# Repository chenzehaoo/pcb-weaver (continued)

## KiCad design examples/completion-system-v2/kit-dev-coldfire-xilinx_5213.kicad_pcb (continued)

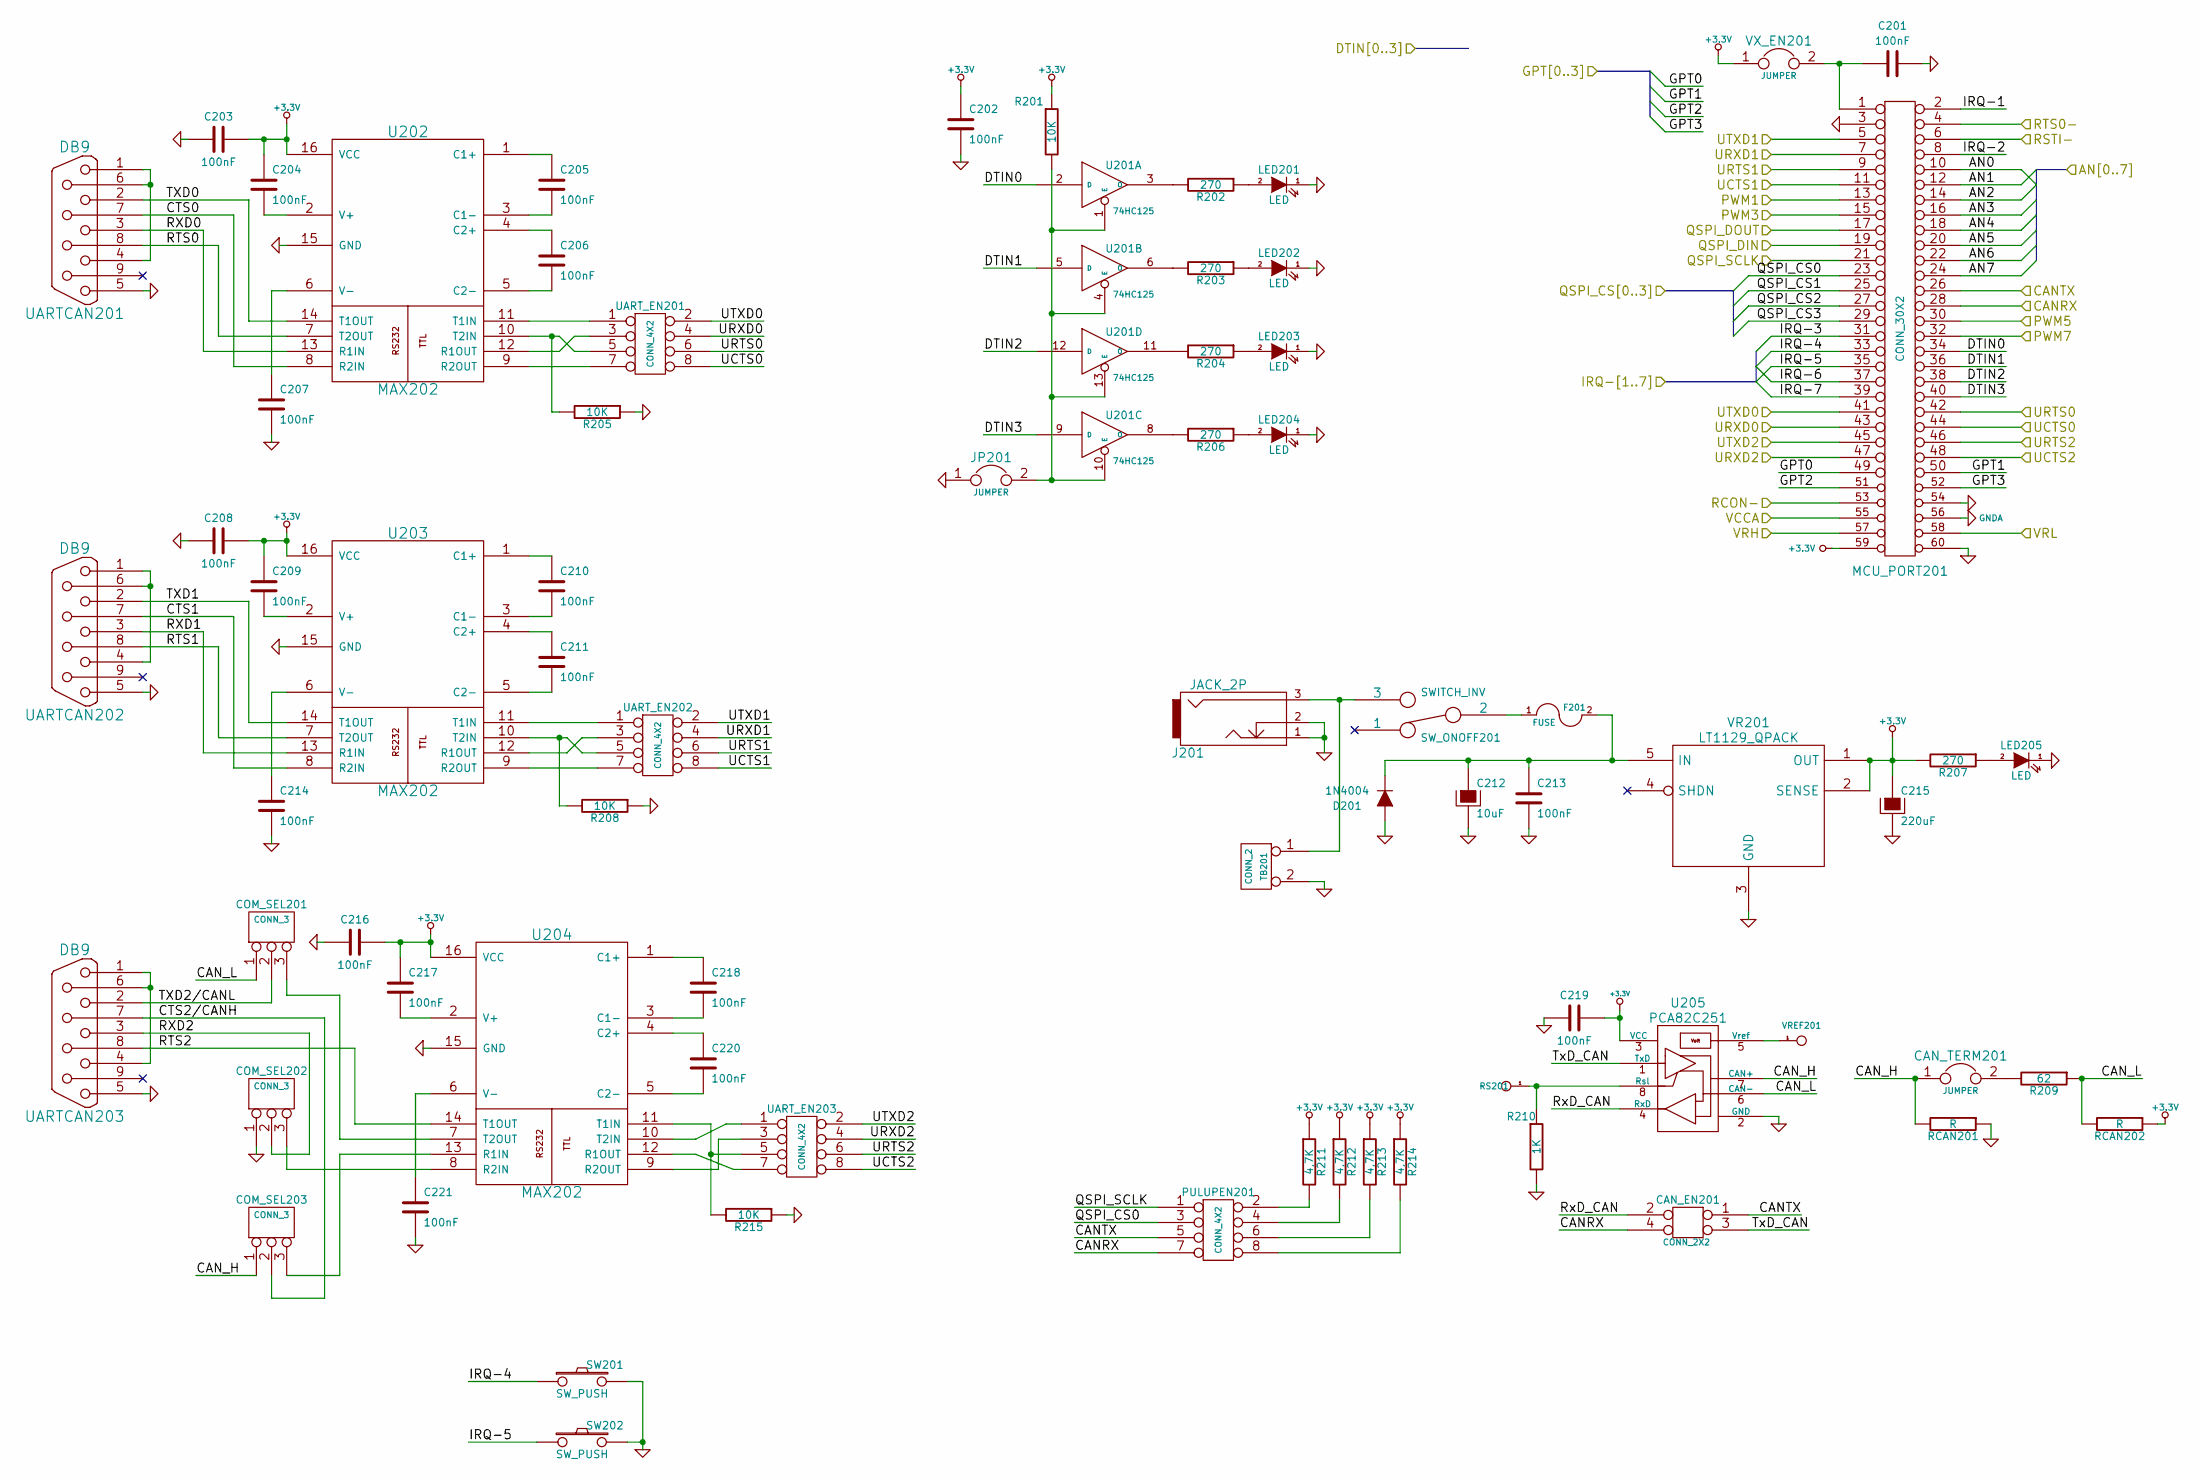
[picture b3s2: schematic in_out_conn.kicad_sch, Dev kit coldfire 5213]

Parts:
C201, C202, C203, C204, C205, C206, C207, C208, C209, C210, C211, C213, C214, C216, C217, C218, C219, C220, C221: 100nF; C_0805_2012Metric
C212: 10uF; CP_Radial_D8.0mm_P5.00mm
C215: 220uF; CP_Radial_D8.0mm_P5.00mm
CAN_EN201: CONN_2X2; PinHeader_2x02_P2.54mm_Vertical
CAN_TERM201: JUMPER; PinHeader_1x02_P2.54mm_Vertical
COM_SEL201, COM_SEL202, COM_SEL203: CONN_3; PinHeader_1x03_P2.54mm_Vertical
D201: 1N4004; D_DO-15_P12.70mm_Horizontal
F201: FUSE; FSUPCMS
J201: JACK_2P; JACK_ALIM
JP201: JUMPER; PinHeader_1x02_P2.54mm_Vertical
LED201, LED202, LED203, LED204, LED205: LED; LED_1206_3216Metric
MCU_PORT201: CONN_30X2; PinHeader_2x30_P2.54mm_Vertical
PULUPEN201: CONN_4X2; PinHeader_2x04_P2.54mm_Vertical
R201, R205, R208, R215: 10K; R_0805_2012Metric
R202, R203, R204, R206, R207: 270; R_0805_2012Metric
R209: 62; R_0805_2012Metric
R210: 1K; R_0805_2012Metric
R211, R212, R213, R214: 4,7K; R_0805_2012Metric
RCAN201, RCAN202: R; R_0805_2012Metric
RS201: CONN_1; PinHeader_1x01_P2.54mm_Vertical
SW201, SW202: SW_PUSH; SW_PUSH_SMALL
SW_ONOFF201: SWITCH_INV; SW_SPDT
TB201: CONN_2; Altech_AK300_1x02_P5.00mm_45-Degree
U201: 74HC125; SOIC-14_3.9x8.7mm_P1.27mm
U202, U203, U204: MAX202; SOIC-16_3.9x9.9mm_P1.27mm
U205: PCA82C251; SOIC-8_3.9x4.9mm_P1.27mm
UARTCAN201, UARTCAN202, UARTCAN203: DB9; DSUB-9_Female_Horizontal_P2.77x2.84mm_EdgePinOffset7.70mm_H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
UART_EN201, UART_EN202, UART_EN203: CONN_4X2; PinHeader_2x04_P2.54mm_Vertical
VR201: LT1129_QPACK; TO-263-5_TabPin3
VREF201: CONN_1; PinHeader_1x01_P2.54mm_Vertical
VX_EN201: JUMPER; PinHeader_1x02_P2.54mm_Vertical

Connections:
+3.3V: C202.1, C203.1, C204.1, C208.1, C209.1, C215.1, C216.1, C217.1, C219.1, MCU_PORT201.59, R201.1, R207.2, R211.1, R212.1, R213.1, R214.1, RCAN202.1, U201.14 (VCC), U202.16 (VCC), U203.16 (VCC), U204.16 (VCC), U205.3 (VCC), VR201.1 (OUT), VR201.2 (SENSE), VX_EN201.1; also elsewhere on the board
/AN0: MCU_PORT201.10; also elsewhere on the board
/AN1: MCU_PORT201.12; also elsewhere on the board
/AN2: MCU_PORT201.14; also elsewhere on the board
/AN3: MCU_PORT201.16; also elsewhere on the board
/AN4: MCU_PORT201.18; also elsewhere on the board
/AN5: MCU_PORT201.20; also elsewhere on the board
/AN6: MCU_PORT201.22; also elsewhere on the board
/AN7: MCU_PORT201.24; also elsewhere on the board
/CANRX: CAN_EN201.4, MCU_PORT201.28, PULUPEN201.7; also elsewhere on the board
/CANTX: CAN_EN201.1, MCU_PORT201.26, PULUPEN201.5; also elsewhere on the board
/DSPI_DOUT: MCU_PORT201.17; also elsewhere on the board
/DTIN0: MCU_PORT201.34, U201.2 (D); also elsewhere on the board
/DTIN1: MCU_PORT201.36, U201.5 (D); also elsewhere on the board
/DTIN2: MCU_PORT201.38, U201.12 (D); also elsewhere on the board
/DTIN3: MCU_PORT201.40, U201.9 (D); also elsewhere on the board
/GPT0: MCU_PORT201.49; also elsewhere on the board
/GPT1: MCU_PORT201.50; also elsewhere on the board
/GPT2: MCU_PORT201.51; also elsewhere on the board
/GPT3: MCU_PORT201.52; also elsewhere on the board
/IRQ-1: MCU_PORT201.2; also elsewhere on the board
/IRQ-2: MCU_PORT201.8; also elsewhere on the board
/IRQ-3: MCU_PORT201.31; also elsewhere on the board
/IRQ-4: MCU_PORT201.33, SW201.1; also elsewhere on the board
/IRQ-5: MCU_PORT201.35, SW202.1; also elsewhere on the board
/IRQ-6: MCU_PORT201.37; also elsewhere on the board
/IRQ-7: MCU_PORT201.39; also elsewhere on the board
/PWM1: MCU_PORT201.13; also elsewhere on the board
/PWM3: MCU_PORT201.15; also elsewhere on the board
/PWM5: MCU_PORT201.30; also elsewhere on the board
/PWM7: MCU_PORT201.32; also elsewhere on the board
/QSPI_CLK: MCU_PORT201.21, PULUPEN201.1; also elsewhere on the board
/QSPI_CS0: MCU_PORT201.23, PULUPEN201.3; also elsewhere on the board
/QSPI_CS1: MCU_PORT201.25; also elsewhere on the board
/QSPI_CS2: MCU_PORT201.27; also elsewhere on the board
/QSPI_CS3: MCU_PORT201.29; also elsewhere on the board
/QSPI_DIN: MCU_PORT201.19; also elsewhere on the board
/RCON-: MCU_PORT201.53; also elsewhere on the board
/RSTI-: MCU_PORT201.6; also elsewhere on the board
/RSTO-: MCU_PORT201.4; also elsewhere on the board
/UCTS0: MCU_PORT201.44, UART_EN201.8; also elsewhere on the board
/UCTS1: MCU_PORT201.11, UART_EN202.8; also elsewhere on the board
/UCTS2: MCU_PORT201.48, UART_EN203.8; also elsewhere on the board
/URTS0: MCU_PORT201.42, UART_EN201.6; also elsewhere on the board
/URTS1: MCU_PORT201.9, UART_EN202.6; also elsewhere on the board
/URTS2: MCU_PORT201.46, UART_EN203.6; also elsewhere on the board
/URXD0: MCU_PORT201.43, UART_EN201.4; also elsewhere on the board
/URXD1: MCU_PORT201.7, UART_EN202.4; also elsewhere on the board
/URXD2: MCU_PORT201.47, UART_EN203.4; also elsewhere on the board
/UTXD0: MCU_PORT201.41, UART_EN201.2; also elsewhere on the board
/UTXD1: MCU_PORT201.5, UART_EN202.2; also elsewhere on the board
/UTXD2: MCU_PORT201.45, UART_EN203.2; also elsewhere on the board
/VCCA: MCU_PORT201.55, MCU_PORT201.57; also elsewhere on the board
/inout_user/CAN_H: CAN_TERM201.1, COM_SEL203.1, RCAN201.2, U205.7 (CAN+)
/inout_user/CAN_L: COM_SEL201.1, R209.1, RCAN202.2, U205.6 (CAN-)
/inout_user/CTS0: U202.8 (R2IN), UARTCAN201.7
/inout_user/CTS1: U203.8 (R2IN), UARTCAN202.7
/inout_user/CTS2/CANH: COM_SEL203.2 (PM), UARTCAN203.7
/inout_user/RTS0: U202.7 (T2OUT), UARTCAN201.8
/inout_user/RTS1: U203.7 (T2OUT), UARTCAN202.8
/inout_user/RTS2: U204.14 (T1OUT), UARTCAN203.8
/inout_user/RXD0: U202.13 (R1IN), UARTCAN201.3
/inout_user/RXD1: U203.13 (R1IN), UARTCAN202.3
/inout_user/RXD2: COM_SEL202.2 (PM), UARTCAN203.3
/inout_user/RxD_CAN: CAN_EN201.2, U205.4 (RxD)
/inout_user/TXD0: U202.14 (T1OUT), UARTCAN201.2
/inout_user/TXD1: U203.14 (T1OUT), UARTCAN202.2
/inout_user/TXD2/CANL: COM_SEL201.2 (PM), UARTCAN203.2
/inout_user/TxD_CAN: CAN_EN201.3, U205.1 (TxD)
GND: C201.1, C202.2, C203.2, C207.2, C208.2, C212.2, C213.2, C214.2, C215.2, C216.2, C219.2, C221.2, COM_SEL202.1, D201.2 (A), J201.1, J201.2, JP201.1, LED201.1 (K), LED202.1 (K), LED203.1 (K), LED204.1 (K), LED205.1 (K), MCU_PORT201.3, MCU_PORT201.54, MCU_PORT201.60, R205.1, R208.1, R210.2, R215.1, RCAN201.1, SW201.2, SW202.2, TB201.2 (PM), U201.7 (GND), U202.15 (GND), U203.15 (GND), U204.15 (GND), U205.2 (GND), UARTCAN201.5, UARTCAN202.5, UARTCAN203.5, VR201.3 (GND); also elsewhere on the board
GNDA: MCU_PORT201.56, MCU_PORT201.58; also elsewhere on the board
unnamed: CAN_TERM201.2, R209.2
unnamed: COM_SEL201.3, U204.7 (T2OUT)
unnamed: COM_SEL202.3, U204.8 (R2IN)
unnamed: COM_SEL203.3, U204.13 (R1IN)
unnamed: C212.1, C213.1, D201.1 (K), F201.2, VR201.5 (IN)
unnamed: F201.1, SW_ONOFF201.2
unnamed: LED201.2 (A), R202.1
unnamed: LED202.2 (A), R203.1
unnamed: LED203.2 (A), R204.1
unnamed: LED204.2 (A), R206.1
unnamed: LED205.2 (A), R207.1
unnamed: C201.2, MCU_PORT201.1, VX_EN201.2
unnamed: PULUPEN201.2, R211.2
unnamed: PULUPEN201.4, R212.2
unnamed: PULUPEN201.6, R213.2
unnamed: PULUPEN201.8, R214.2
unnamed: J201.3, SW_ONOFF201.3, TB201.1
unnamed: JP201.2, R201.2, U201.1 (E), U201.4 (E), U201.10 (E), U201.13 (E)
unnamed: R202.2, U201.3 (O)
unnamed: R203.2, U201.6 (O)
unnamed: R206.2, U201.8 (O)
unnamed: R204.2, U201.11 (O)
unnamed: C205.1, U202.1 (C1+)
unnamed: C205.2, U202.3 (C1-)
unnamed: C206.1, U202.4 (C2+)
unnamed: C206.2, U202.5 (C2-)
unnamed: U202.12 (R1OUT), UART_EN201.3
unnamed: U202.9 (R2OUT), UART_EN201.7
unnamed: U202.11 (T1IN), UART_EN201.1
unnamed: R205.2, U202.10 (T2IN), UART_EN201.5
unnamed: C204.2, U202.2 (V+)
unnamed: C207.1, U202.6 (V-)
unnamed: C210.1, U203.1 (C1+)
unnamed: C210.2, U203.3 (C1-)
unnamed: C211.1, U203.4 (C2+)
unnamed: C211.2, U203.5 (C2-)
unnamed: U203.12 (R1OUT), UART_EN202.3
unnamed: U203.9 (R2OUT), UART_EN202.7
unnamed: U203.11 (T1IN), UART_EN202.1
unnamed: R208.2, U203.10 (T2IN), UART_EN202.5
unnamed: C209.2, U203.2 (V+)
unnamed: C214.1, U203.6 (V-)
unnamed: C218.1, U204.1 (C1+)
unnamed: C218.2, U204.3 (C1-)
unnamed: C220.1, U204.4 (C2+)
unnamed: C220.2, U204.5 (C2-)
unnamed: U204.12 (R1OUT), UART_EN203.7
unnamed: U204.9 (R2OUT), UART_EN203.3
unnamed: R215.2, U204.11 (T1IN), UART_EN203.5
unnamed: U204.10 (T2IN), UART_EN203.1
unnamed: C217.2, U204.2 (V+)
unnamed: C221.1, U204.6 (V-)
unnamed: R210.1, RS201.1, U205.8 (Rsl)
unnamed: U205.5 (Vref), VREF201.1
unnamed: UARTCAN201.1, UARTCAN201.4, UARTCAN201.6
unnamed: UARTCAN202.1, UARTCAN202.4, UARTCAN202.6
unnamed: UARTCAN203.1, UARTCAN203.4, UARTCAN203.6

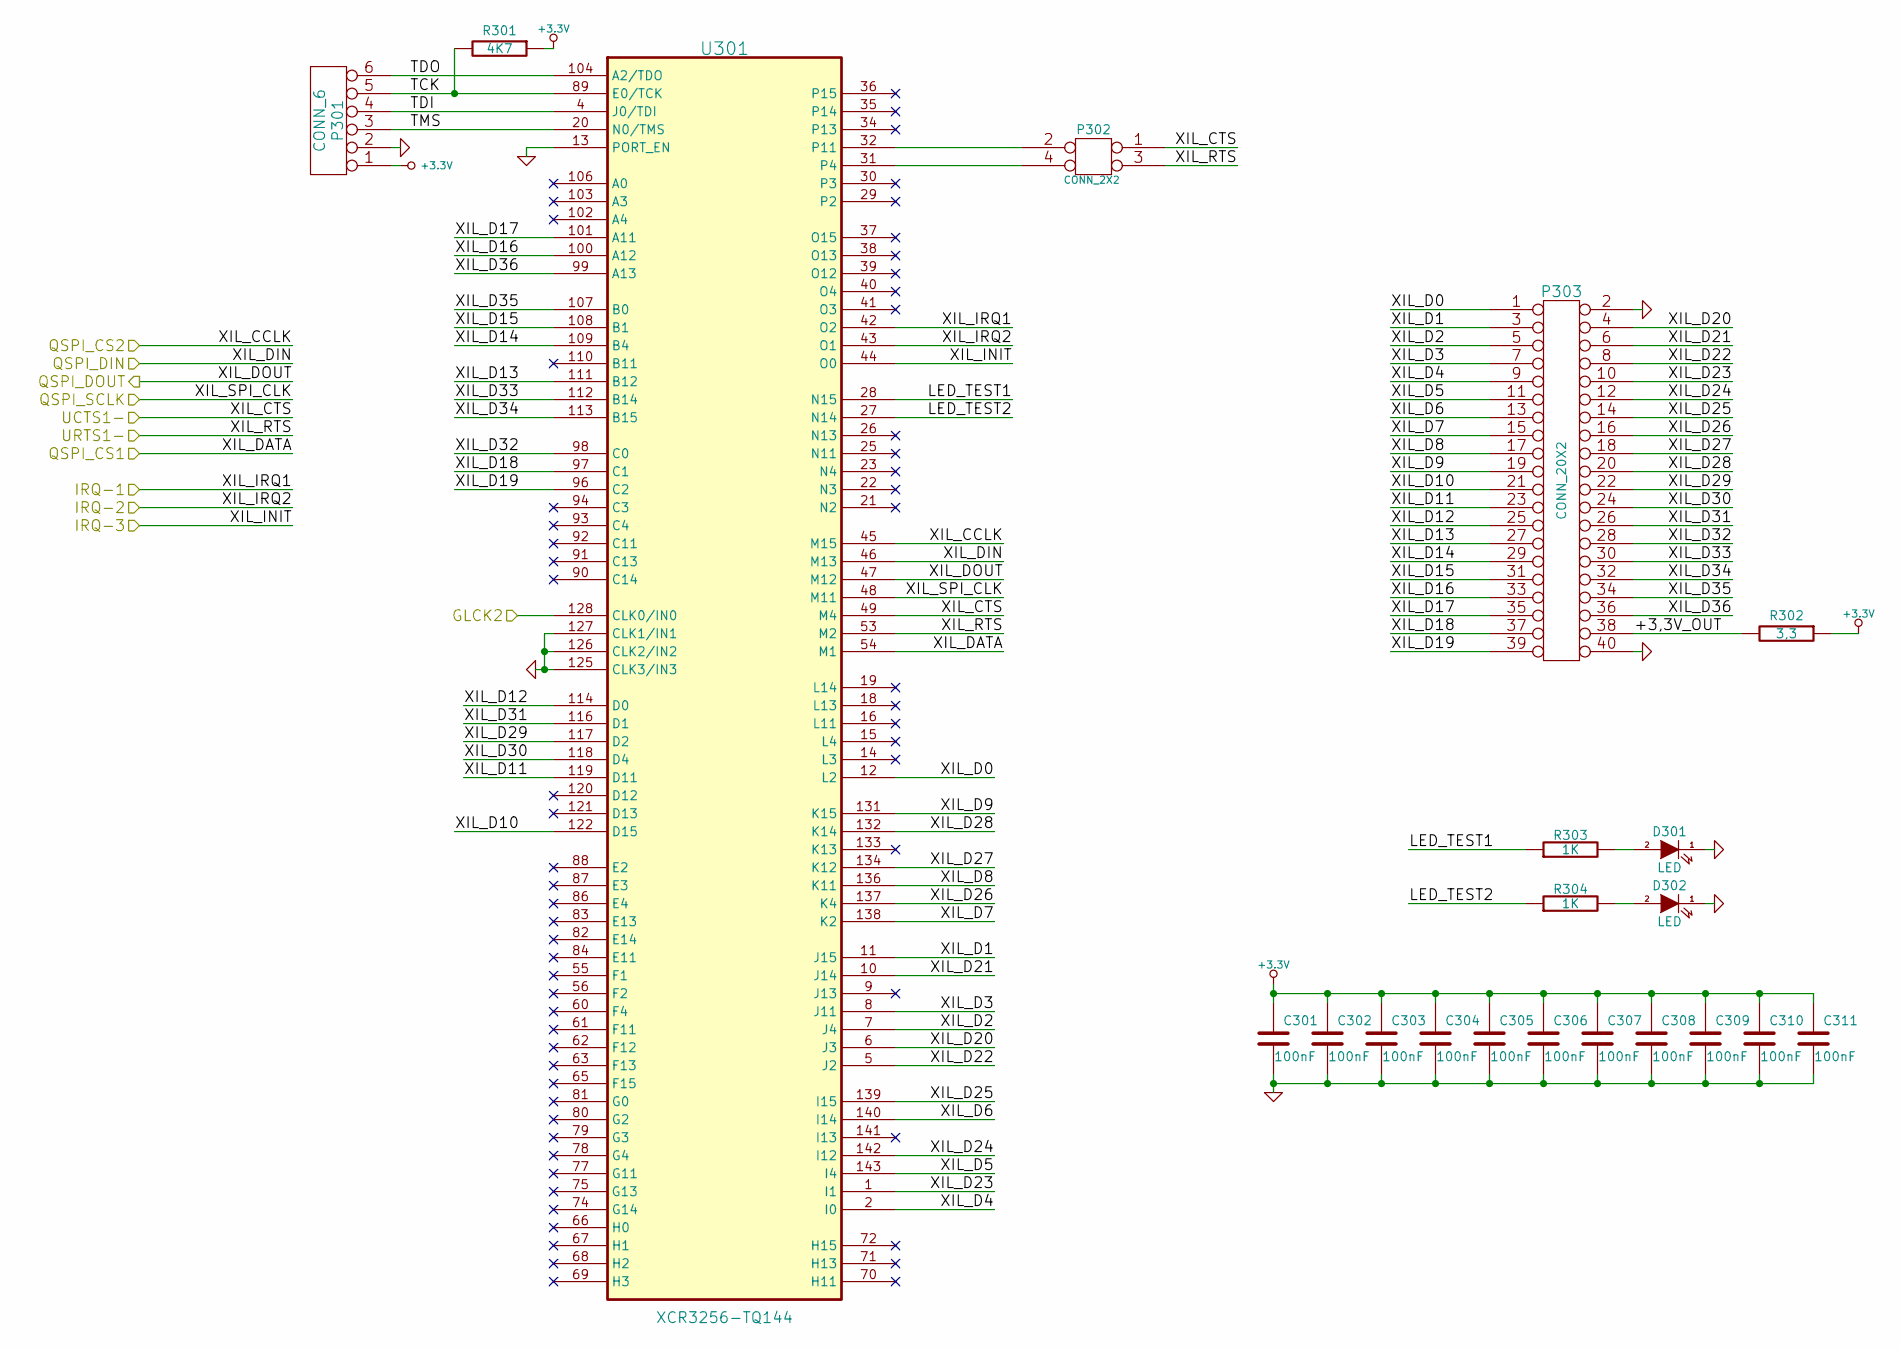
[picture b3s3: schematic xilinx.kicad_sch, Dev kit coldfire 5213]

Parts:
C301, C302, C303, C304, C305, C306, C307, C308, C309, C310, C311: 100nF; C_0805_2012Metric
D301, D302: LED; LED_1206_3216Metric
P301: CONN_6; PinHeader_1x06_P2.54mm_Vertical
P302: CONN_2X2; PinHeader_2x02_P2.54mm_Vertical
P303: CONN_20X2; PinHeader_2x20_P2.54mm_Vertical
R301: 4K7; R_0805_2012Metric
R302: 3,3; R_Axial_DIN0207_L6.3mm_D2.5mm_P10.16mm_Horizontal
R303, R304: 1K; R_0805_2012Metric
U301: XCR3256-TQ144; TQFP-144_20x20mm_P0.5mm

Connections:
+3.3V: C301.1, C302.1, C303.1, C304.1, C305.1, C306.1, C307.1, C308.1, C309.1, C310.1, C311.1, P301.1, R301.1, R302.1, U301.24 (VCC), U301.50 (VCC), U301.51 (VCC), U301.58 (VCC), U301.73 (VCC), U301.76 (VCC), U301.95 (VCC), U301.115 (VCC), U301.123 (VCC), U301.130 (VCC), U301.144 (VCC); also elsewhere on the board
/DSPI_DOUT: U301.47 (M12); also elsewhere on the board
/IRQ-1: U301.42 (O2); also elsewhere on the board
/IRQ-2: U301.43 (O1); also elsewhere on the board
/IRQ-3: U301.44 (O0); also elsewhere on the board
/QSPI_CLK: U301.48 (M11); also elsewhere on the board
/QSPI_CS1: U301.54 (M1); also elsewhere on the board
/QSPI_CS2: U301.45 (M15); also elsewhere on the board
/QSPI_DIN: U301.46 (M13); also elsewhere on the board
/UCTS1: P302.1, U301.49 (M4); also elsewhere on the board
/URTS1: P302.3, U301.53 (M2); also elsewhere on the board
/XTAL: U301.128 (CLK0/IN0); also elsewhere on the board
/xilinx/+3,3V_OUT: P303.38, R302.2
/xilinx/LED_TEST1: R303.1, U301.28 (N15)
/xilinx/LED_TEST2: R304.1, U301.27 (N14)
/xilinx/TCK: P301.5, R301.2, U301.89 (E0/TCK)
/xilinx/TDI: P301.4, U301.4 (J0/TDI)
/xilinx/TDO: P301.6, U301.104 (A2/TDO)
/xilinx/TMS: P301.3, U301.20 (N0/TMS)
/xilinx/XIL_D0: P303.1, U301.12 (L2)
/xilinx/XIL_D1: P303.3, U301.11 (J15)
/xilinx/XIL_D2: P303.5, U301.7 (J4)
/xilinx/XIL_D3: P303.7, U301.8 (J11)
/xilinx/XIL_D4: P303.9, U301.2 (I0)
/xilinx/XIL_D5: P303.11, U301.143 (I4)
/xilinx/XIL_D6: P303.13, U301.140 (I14)
/xilinx/XIL_D7: P303.15, U301.138 (K2)
/xilinx/XIL_D8: P303.17, U301.136 (K11)
/xilinx/XIL_D9: P303.19, U301.131 (K15)
/xilinx/XIL_D10: P303.21, U301.122 (D15)
/xilinx/XIL_D11: P303.23, U301.119 (D11)
/xilinx/XIL_D12: P303.25, U301.114 (D0)
/xilinx/XIL_D13: P303.27, U301.111 (B12)
/xilinx/XIL_D14: P303.29, U301.109 (B4)
/xilinx/XIL_D15: P303.31, U301.108 (B1)
/xilinx/XIL_D16: P303.33, U301.100 (A12)
/xilinx/XIL_D17: P303.35, U301.101 (A11)
/xilinx/XIL_D18: P303.37, U301.97 (C1)
/xilinx/XIL_D19: P303.39, U301.96 (C2)
/xilinx/XIL_D20: P303.4, U301.6 (J3)
/xilinx/XIL_D21: P303.6, U301.10 (J14)
/xilinx/XIL_D22: P303.8, U301.5 (J2)
/xilinx/XIL_D23: P303.10, U301.1 (I1)
/xilinx/XIL_D24: P303.12, U301.142 (I12)
/xilinx/XIL_D25: P303.14, U301.139 (I15)
/xilinx/XIL_D26: P303.16, U301.137 (K4)
/xilinx/XIL_D27: P303.18, U301.134 (K12)
/xilinx/XIL_D28: P303.20, U301.132 (K14)
/xilinx/XIL_D29: P303.22, U301.117 (D2)
/xilinx/XIL_D30: P303.24, U301.118 (D4)
/xilinx/XIL_D31: P303.26, U301.116 (D1)
/xilinx/XIL_D32: P303.28, U301.98 (C0)
/xilinx/XIL_D33: P303.30, U301.112 (B14)
/xilinx/XIL_D34: P303.32, U301.113 (B15)
/xilinx/XIL_D35: P303.34, U301.107 (B0)
/xilinx/XIL_D36: P303.36, U301.99 (A13)
GND: C301.2, C302.2, C303.2, C304.2, C305.2, C306.2, C307.2, C308.2, C309.2, C310.2, C311.2, D301.1 (K), D302.1 (K), P301.2, P303.2, P303.40, U301.3 (GND), U301.13 (PORT_EN), U301.17 (GND), U301.33 (GND), U301.52 (GND), U301.57 (GND), U301.59 (GND), U301.64 (GND), U301.85 (GND), U301.105 (GND), U301.124 (GND), U301.125 (CLK3/IN3), U301.126 (CLK2/IN2), U301.127 (CLK1/IN1), U301.129 (GND), U301.135 (GND); also elsewhere on the board
unnamed: D301.2 (A), R303.2
unnamed: D302.2 (A), R304.2
unnamed: P302.4, U301.31 (P4)
unnamed: P302.2, U301.32 (P11)

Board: 4 copper layers, 160 parts (14 on the bottom side), 209 nets, no tracks yet.

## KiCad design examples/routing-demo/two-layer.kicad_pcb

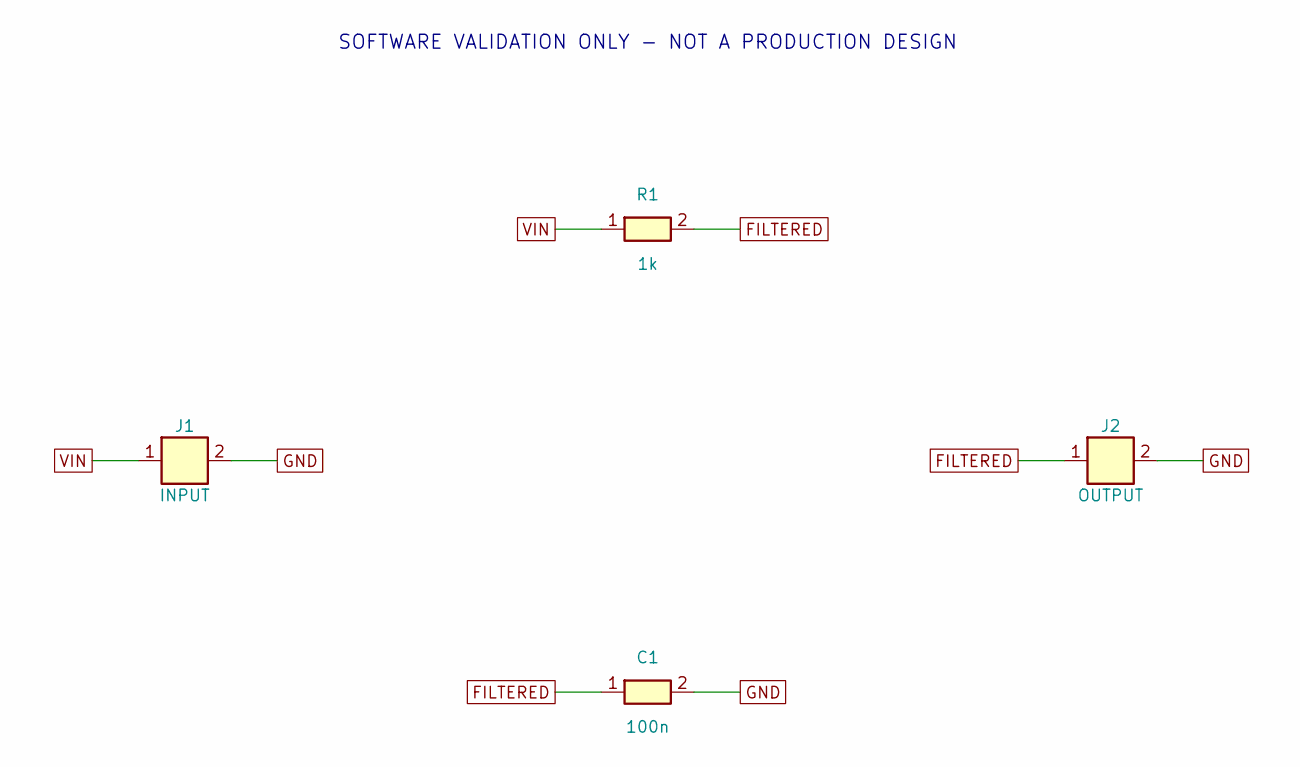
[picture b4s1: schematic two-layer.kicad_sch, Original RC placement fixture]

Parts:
C1: 100n; PassiveFixture
J1: INPUT; TwoPinFixture
J2: OUTPUT; TwoPinFixture
R1: 1k; PassiveFixture

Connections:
FILTERED: C1.1, J2.1, R1.2
GND: C1.2, J1.2, J2.2
VIN: J1.1, R1.1

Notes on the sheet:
SOFTWARE VALIDATION ONLY - NOT A PRODUCTION DESIGN

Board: 2 copper layers, 4 parts (0 on the bottom side), 3 nets, no tracks yet.
